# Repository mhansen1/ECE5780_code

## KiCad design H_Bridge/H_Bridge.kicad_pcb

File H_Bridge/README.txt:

Can probably take out resistors R1 through R6. Don't think that they are needed since the L298 uses BJTs, which are based on the amount of current to the base (versus MOSFETs, which are based on the voltage applied to the gate).
The reason that they were originally there is to help and make sure that no "rogue" signals from the master triggered them to go high, but because the inputs to the L298 are logic gates, the input can already be thought of as high impedance.

R7 and R8 are the sense resistors. They are at only 1 Ohm because the processor's ADC converts voltages between 0 and 3.6V, and I'm assuming a peak current of 3 Amps (even though the stall current is 5 Amps, but I'm going to assume
for now that we wont run into that). So that means 3.6V/3A=1.2 which is close enough to 1A. And I found some 10 Watt resistors, so too much power shouldn't be an issue.

The LEDs are to indicate the state of the inputs into the H bridge.

The diodes are flyback diodes. They protect against back EMF and the effect of inductive loads (and a motor is basically a giant inductor).
The capacitors are kind of big because of the LEDs and diodes. They are meant to smooth out any noise and deal with power spikes.

The capacitors are at 0.22uF because of the other all the components in the design (LEDs, temp. sensor, etc...). These can be upped to a higher standard value if needed, at least on the Vdd line, since that's where all of the other "extra"
components are.

The resistor on the OS input of the is a pull-up resistor. According to the data sheet, a pull-up resistor (or at least a tie to high voltage) is needed in order to get an output from the temperature sensor's interrupt line. If it does not have this,
no high signal can be read from it (it's essentially useless, then). Also, on the temperature sensor, I left the inputs A2, A1, and A0 unconnected. This is because it looks like they are a way to address the sensor in a parallel method. However, 
this can be be done in a serial method over the I2C line (SD, which I named as the short for "serial data"). This is to reduce the amount of data lines needed.

Also, because we are doing PCB, I don't think that we need to worry about input/output pins. It just did it as though we were going to screw terminals. If we were doing it as pins that need to go to another circuit (such as for simulation), then
the screw terminals would be replaced with inputs/output ports.

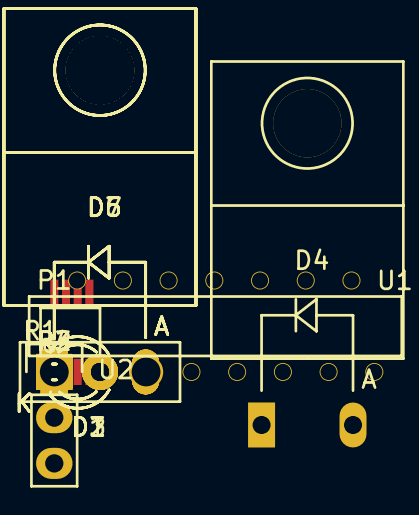
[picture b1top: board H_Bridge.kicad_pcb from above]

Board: 2 copper layers, 14 parts (0 on the bottom side), 12 nets, no tracks yet.

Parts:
D1, D2, D3: LED; LED-3MM
D4, D5, D6, D7: D; Diode_TO-220_Horizontal
P1: CONN_01X03; Pin_Header_Straight_1x03
R1: PF1262
R2, R3, R4: 10k; R_0201
U1: L298
U2: LM75A

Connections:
+3V3: R2.1, R3.1, R4.1, U2.8
+6V: D4.1, D5.1, U1.4
GND: D1.1, D2.1, D3.1, D6.2, D7.2, R1.2, U1.8, U2.4, U2.5, U2.6, U2.7
unnamed: D4.2, D6.1, U1.2, U1.14
unnamed: D5.2, D7.1, U1.3, U1.13
unnamed: R1.1, U1.1, U1.15
unnamed: P1.1, U1.5, U1.12
unnamed: P1.2, U1.7, U1.10
unnamed: P1.3, U1.6, U1.11
unnamed: R4.2, U2.2
unnamed: R3.2, U2.1
unnamed: R2.2, U2.3
